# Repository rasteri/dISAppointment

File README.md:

# dISAppointment
Adding ISA slots to modern motherboards

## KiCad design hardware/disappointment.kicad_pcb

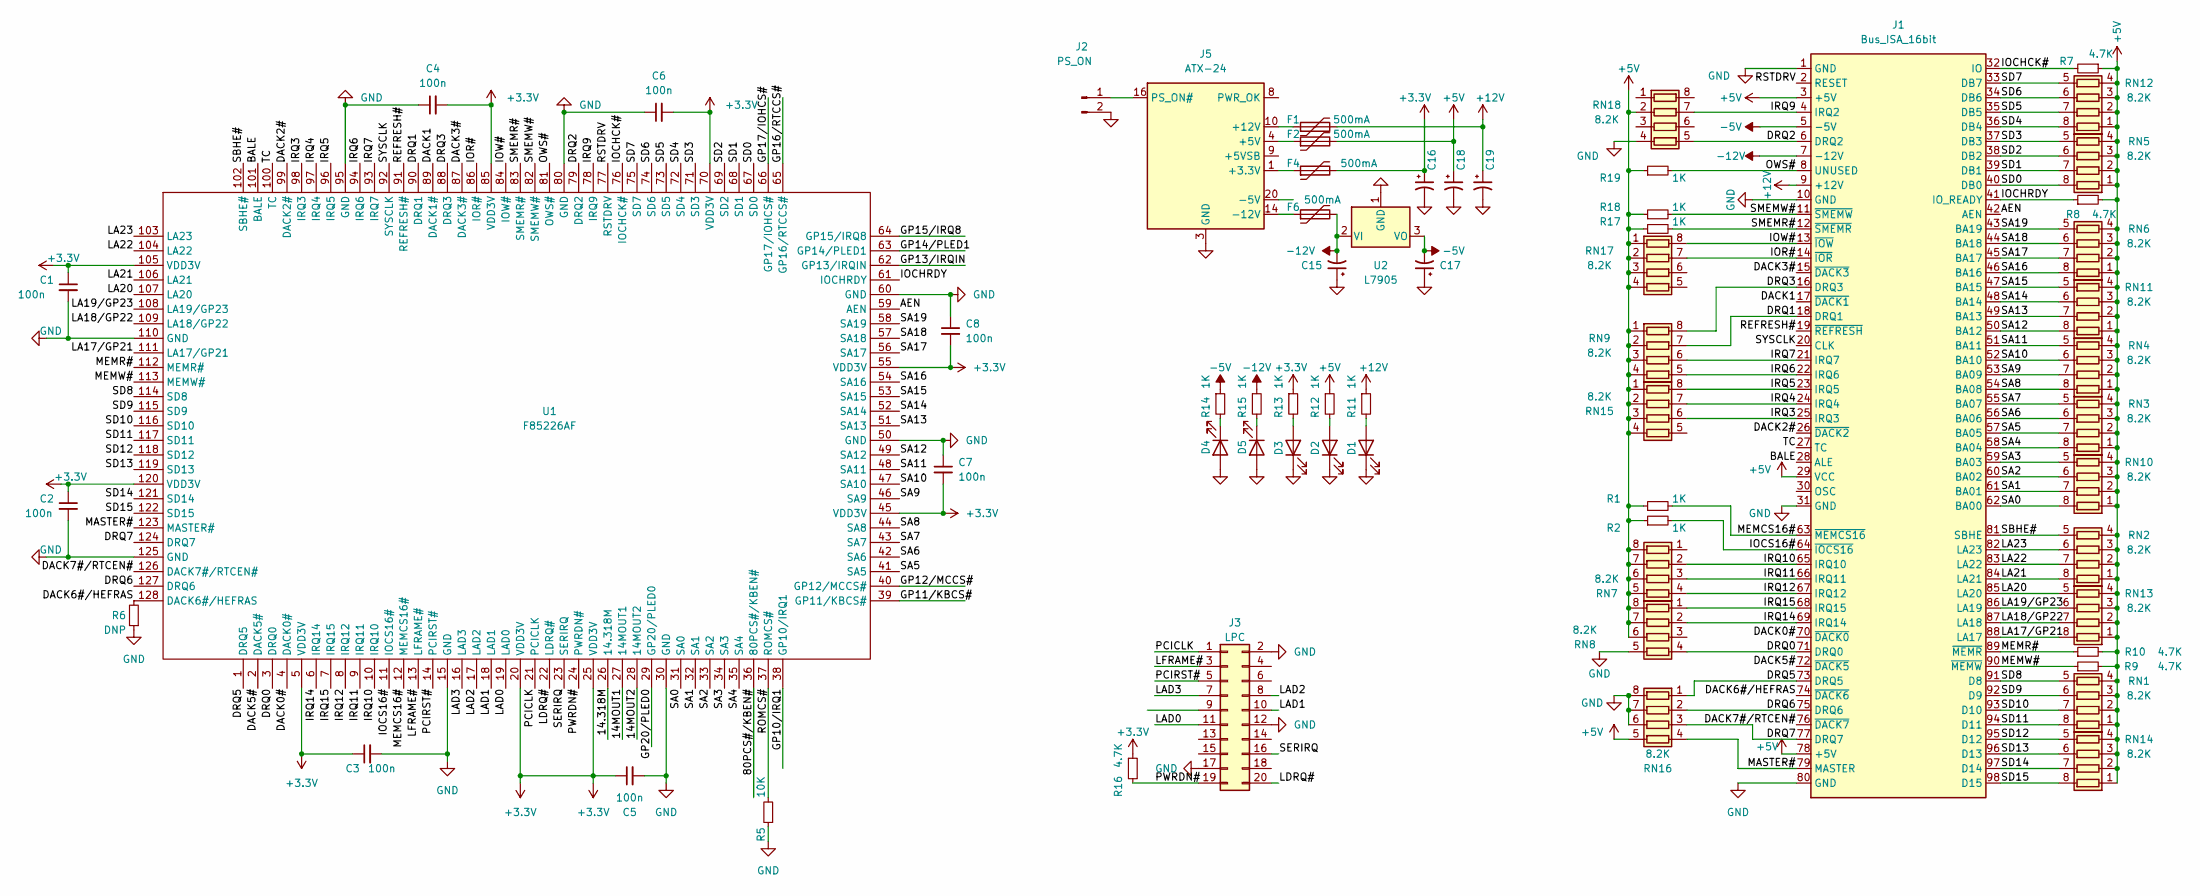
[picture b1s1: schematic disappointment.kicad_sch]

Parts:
C1, C2, C3, C4, C5, C6, C7, C8: 100n; C_1206_3216Metric
C15, C16, C17, C18, C19: 10uF; CP_Radial_D5.0mm_P2.50mm
D1, D2, D3, D4, D5: LED; LED_1206_3216Metric
F1, F2, F4, F6: 500mA; Fuse_1206_3216Metric
J1: Bus_ISA_16bit; ISA
J2: PS_ON; PinHeader_1x02_P2.54mm_Vertical
J3: LPC; PinHeader_2x10_P2.54mm_Vertical
J5: ATX-24; Molex_Mini-Fit_Jr_5566-24A_2x12_P4.20mm_Vertical
R1, R2, R11, R12, R13, R14, R15, R17, R18, R19: 1K; R_1206_3216Metric_Pad1.30x1.75mm_HandSolder
R5: 10K; R_1206_3216Metric_Pad1.30x1.75mm_HandSolder
R6: DNP; R_1206_3216Metric_Pad1.30x1.75mm_HandSolder
R7, R8, R9, R10, R16: 4.7K; R_1206_3216Metric_Pad1.30x1.75mm_HandSolder
RN1, RN2, RN3, RN4, RN5, RN6, RN7, RN8, RN9, RN10, RN11, RN12, RN13, RN14, RN15, RN16, RN17, RN18: 8.2K; R_Array_Concave_4x0603
U1: F85226AF; QFP-26x38_14x20_Pitch0.5mm
U2: L7905; TO-220-3_Vertical

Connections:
+3.3V: C1.1, C2.1, C3.1, C4.2, C5.1, C6.2, C7.2, C8.2, C16.1, F4.2, R13.1, R16.1, U1.5 (VDD3V), U1.20 (VDD3V), U1.25 (VDD3V), U1.45 (VDD3V), U1.55 (VDD3V), U1.70 (VDD3V), U1.85 (VDD3V), U1.105 (VDD3V), U1.120 (VDD3V)
+5V: C18.1, F2.2, J1.3 (+5V), J1.29 (VCC), J1.78 (+5V), R1.1, R2.1, R7.1, R8.2, R9.2, R10.2, R12.1, R17.1, R18.1, R19.1, RN1.1 (R1.1), RN1.2 (R2.1), RN1.3 (R3.1), RN1.4 (R4.1), RN2.1 (R1.1), RN2.2 (R2.1), RN2.3 (R3.1), RN2.4 (R4.1), RN3.1 (R1.1), RN3.2 (R2.1), RN3.3 (R3.1), RN3.4 (R4.1), RN4.1 (R1.1), RN4.2 (R2.1), RN4.3 (R3.1), RN4.4 (R4.1), RN5.1 (R1.1), RN5.2 (R2.1), RN5.3 (R3.1), RN5.4 (R4.1), RN6.1 (R1.1), RN6.2 (R2.1), RN6.3 (R3.1), RN6.4 (R4.1), RN7.5 (R4.2), RN7.6 (R3.2), RN7.7 (R2.2), RN7.8 (R1.2), RN8.6 (R3.2), RN8.7 (R2.2), RN8.8 (R1.2), RN9.1 (R1.1), RN9.2 (R2.1), RN9.3 (R3.1), RN9.4 (R4.1), RN10.1 (R1.1), RN10.2 (R2.1), RN10.3 (R3.1), RN10.4 (R4.1), RN11.1 (R1.1), RN11.2 (R2.1), RN11.3 (R3.1), RN11.4 (R4.1), RN12.1 (R1.1), RN12.2 (R2.1), RN12.3 (R3.1), RN12.4 (R4.1), RN13.1 (R1.1), RN13.2 (R2.1), RN13.3 (R3.1), RN13.4 (R4.1), RN14.1 (R1.1), RN14.2 (R2.1), RN14.3 (R3.1), RN14.4 (R4.1), RN15.1 (R1.1), RN15.2 (R2.1), RN15.3 (R3.1), RN15.4 (R4.1), RN16.5 (R4.2), RN17.1 (R1.1), RN17.2 (R2.1), RN17.3 (R3.1), RN17.4 (R4.1), RN18.2 (R2.1)
+12V: C19.1, F1.2, J1.9 (+12V), R11.1
-5V: C17.2, J1.5 (-5V), R14.1, U2.3 (VO)
-12V: C15.2, F6.2, J1.7 (-12V), R15.1, U2.2 (VI)
/14.318M: U1.26 (14.318M)
/14MOUT1: U1.27 (14MOUT1)
/14MOUT2: U1.28 (14MOUT2)
/80PCS#/KBEN#: U1.36 (80PCS#/KBEN#)
/AEN: J1.42 (AEN), U1.59 (AEN)
/BALE: J1.28 (ALE), U1.101 (BALE)
/DACK0#: J1.70 (~DACK0), U1.4 (DACK0#)
/DACK1: J1.17 (~DACK1), U1.89 (DACK1#)
/DACK2#: J1.26 (~DACK2), U1.99 (DACK2#)
/DACK3#: J1.15 (~DACK3), U1.87 (DACK3#)
/DACK5#: J1.72 (~DACK5), U1.2 (DACK5#)
/DACK6#/HEFRAS: J1.74 (~DACK6), R6.2, U1.128 (DACK6#/HEFRAS)
/DACK7#/RTCEN#: J1.76 (~DACK7), U1.126 (DACK7#/RTCEN#)
/DRQ0: J1.71 (DRQ0), RN8.4 (R4.1), U1.3 (DRQ0)
/DRQ1: J1.18 (DRQ1), RN9.7 (R2.2), U1.90 (DRQ1)
/DRQ2: J1.6 (DRQ2), RN18.5 (R4.2), U1.79 (DRQ2)
/DRQ3: J1.16 (DRQ3), RN9.8 (R1.2), U1.88 (DRQ3)
/DRQ5: J1.73 (DRQ5), RN16.1 (R1.1), U1.1 (DRQ5)
/DRQ6: J1.75 (DRQ6), RN16.2 (R2.1), U1.127 (DRQ6)
/DRQ7: J1.77 (DRQ7), RN16.3 (R3.1), U1.124 (DRQ7)
/GP10/IRQ1: U1.38 (GP10/IRQ1)
/GP11/KBCS#: U1.39 (GP11/KBCS#)
/GP12/MCCS#: U1.40 (GP12/MCCS#)
/GP13/IRQIN: U1.62 (GP13/IRQIN)
/GP14/PLED1: U1.63 (GP14/PLED1)
/GP15/IRQ8: U1.64 (GP15/IRQ8)
/GP16/RTCCS#: U1.65 (GP16/RTCCS#)
/GP17/IOHCS#: U1.66 (GP17/IOHCS#)
/GP20/PLED0: U1.29 (GP20/PLED0)
/IOCHCK#: J1.32 (IO), R7.2, U1.76 (IOCHCK#)
/IOCHRDY: J1.41 (IO_READY), R8.1, U1.61 (IOCHRDY)
/IOCS16#: J1.64 (~IOCS16), R2.2, U1.11 (IOCS16#)
/IOR#: J1.14 (~IOR), RN17.7 (R2.2), U1.86 (IOR#)
/IOW#: J1.13 (~IOW), RN17.8 (R1.2), U1.84 (IOW#)
/IRQ3: J1.25 (IRQ3), RN15.6 (R3.2), U1.98 (IRQ3)
/IRQ4: J1.24 (IRQ4), RN15.7 (R2.2), U1.97 (IRQ4)
/IRQ5: J1.23 (IRQ5), RN15.8 (R1.2), U1.96 (IRQ5)
/IRQ6: J1.22 (IRQ6), RN9.5 (R4.2), U1.94 (IRQ6)
/IRQ7: J1.21 (IRQ7), RN9.6 (R3.2), U1.93 (IRQ7)
/IRQ9: J1.4 (IRQ2), RN18.7 (R2.2), U1.78 (IRQ9)
/IRQ10: J1.65 (IRQ10), RN7.2 (R2.1), U1.10 (IRQ10)
/IRQ11: J1.66 (IRQ11), RN7.3 (R3.1), U1.9 (IRQ11)
/IRQ12: J1.67 (IRQ12), RN7.4 (R4.1), U1.8 (IRQ12)
/IRQ14: J1.69 (IRQ14), RN8.2 (R2.1), U1.6 (IRQ14)
/IRQ15: J1.68 (IRQ15), RN8.1 (R1.1), U1.7 (IRQ15)
/LA17/GP21: J1.88 (LA17), RN13.8 (R1.2), U1.111 (LA17/GP21)
/LA18/GP22: J1.87 (LA18), RN13.7 (R2.2), U1.109 (LA18/GP22)
/LA19/GP23: J1.86 (LA19), RN13.6 (R3.2), U1.108 (LA19/GP23)
/LA20: J1.85 (LA20), RN13.5 (R4.2), U1.107 (LA20)
/LA21: J1.84 (LA21), RN2.8 (R1.2), U1.106 (LA21)
/LA22: J1.83 (LA22), RN2.7 (R2.2), U1.104 (LA22)
/LA23: J1.82 (LA23), RN2.6 (R3.2), U1.103 (LA23)
/LAD0: J3.11, U1.19 (LAD0)
/LAD1: J3.10, U1.18 (LAD1)
/LAD2: J3.8, U1.17 (LAD2)
/LAD3: J3.7, U1.16 (LAD3)
/LDRQ#: J3.20, U1.22 (LDRQ#)
/LFRAME#: J3.3, U1.13 (LFRAME#)
/MASTER#: J1.79 (MASTER), RN16.4 (R4.1), U1.123 (MASTER#)
/MEMCS16#: J1.63 (~MEMCS16), R1.2, U1.12 (MEMCS16#)
/MEMR#: J1.89 (~MEMR), R10.1, U1.112 (MEMR#)
/MEMW#: J1.90 (~MEMW), R9.1, U1.113 (MEMW#)
/OWS#: J1.8 (UNUSED), R19.2, U1.81 (OWS#)
/PCICLK: J3.1, U1.21 (PCICLK)
/PCIRST#: J3.5, U1.14 (PCIRST#)
/PWRDN#: J3.19, R16.2, U1.24 (PWRDN#)
/REFRESH#: J1.19 (~REFRESH), U1.91 (REFRESH#)
/ROMCS#: R5.2, U1.37 (ROMCS#)
/RSTDRV: J1.2 (RESET), U1.77 (RSTDRV)
/SA0: J1.62 (BA00), RN10.8 (R1.2), U1.31 (SA0)
/SA1: J1.61 (BA01), RN10.7 (R2.2), U1.32 (SA1)
/SA2: J1.60 (BA02), RN10.6 (R3.2), U1.33 (SA2)
/SA3: J1.59 (BA03), RN10.5 (R4.2), U1.34 (SA3)
/SA4: J1.58 (BA04), RN3.8 (R1.2), U1.35 (SA4)
/SA5: J1.57 (BA05), RN3.7 (R2.2), U1.41 (SA5)
/SA6: J1.56 (BA06), RN3.6 (R3.2), U1.42 (SA6)
/SA7: J1.55 (BA07), RN3.5 (R4.2), U1.43 (SA7)
/SA8: J1.54 (BA08), RN4.8 (R1.2), U1.44 (SA8)
/SA9: J1.53 (BA09), RN4.7 (R2.2), U1.46 (SA9)
/SA10: J1.52 (BA10), RN4.6 (R3.2), U1.47 (SA10)
/SA11: J1.51 (BA11), RN4.5 (R4.2), U1.48 (SA11)
/SA12: J1.50 (BA12), RN11.8 (R1.2), U1.49 (SA12)
/SA13: J1.49 (BA13), RN11.7 (R2.2), U1.51 (SA13)
/SA14: J1.48 (BA14), RN11.6 (R3.2), U1.52 (SA14)
/SA15: J1.47 (BA15), RN11.5 (R4.2), U1.53 (SA15)
/SA16: J1.46 (BA16), RN6.8 (R1.2), U1.54 (SA16)
/SA17: J1.45 (BA17), RN6.7 (R2.2), U1.56 (SA17)
/SA18: J1.44 (BA18), RN6.6 (R3.2), U1.57 (SA18)
/SA19: J1.43 (BA19), RN6.5 (R4.2), U1.58 (SA19)
/SBHE#: J1.81 (SBHE), RN2.5 (R4.2), U1.102 (SBHE#)
/SD0: J1.40 (DB0), RN5.8 (R1.2), U1.67 (SD0)
/SD1: J1.39 (DB1), RN5.7 (R2.2), U1.68 (SD1)
/SD2: J1.38 (DB2), RN5.6 (R3.2), U1.69 (SD2)
/SD3: J1.37 (DB3), RN5.5 (R4.2), U1.71 (SD3)
/SD4: J1.36 (DB4), RN12.8 (R1.2), U1.72 (SD4)
/SD5: J1.35 (DB5), RN12.7 (R2.2), U1.73 (SD5)
/SD6: J1.34 (DB6), RN12.6 (R3.2), U1.74 (SD6)
/SD7: J1.33 (DB7), RN12.5 (R4.2), U1.75 (SD7)
/SD8: J1.91 (D8), RN1.5 (R4.2), U1.114 (SD8)
/SD9: J1.92 (D9), RN1.6 (R3.2), U1.115 (SD9)
/SD10: J1.93 (D10), RN1.7 (R2.2), U1.116 (SD10)
/SD11: J1.94 (D11), RN1.8 (R1.2), U1.117 (SD11)
/SD12: J1.95 (D12), RN14.5 (R4.2), U1.118 (SD12)
/SD13: J1.96 (D13), RN14.6 (R3.2), U1.119 (SD13)
/SD14: J1.97 (D14), RN14.7 (R2.2), U1.121 (SD14)
/SD15: J1.98 (D15), RN14.8 (R1.2), U1.122 (SD15)
/SERIRQ: J3.16, U1.23 (SERIRQ)
/SMEMR#: J1.12 (~SMEMR), R17.2, U1.83 (SMEMR#)
/SMEMW#: J1.11 (~SMEMW), R18.2, U1.82 (SMEMW#)
/SYSCLK: J1.20 (CLK), U1.92 (SYSCLK)
/TC: J1.27 (TC), U1.100 (TC)
GND: C1.2, C2.2, C3.2, C4.1, C5.2, C6.1, C7.1, C8.1, C15.1, C16.2, C17.1, C18.2, C19.2, D1.1 (K), D2.1 (K), D3.1 (K), D4.2 (A), D5.2 (A), J1.1 (GND), J1.10 (GND), J1.31 (GND), J1.80 (GND), J2.2, J3.2, J3.12, J3.17, J5.3 (GND), J5.5 (GND), J5.7 (GND), J5.15 (GND), J5.17 (GND), J5.18 (GND), J5.19 (GND), J5.24 (GND), R5.1, R6.1, RN8.5 (R4.2), RN16.6 (R3.2), RN16.7 (R2.2), RN16.8 (R1.2), RN18.4 (R4.1), U1.15 (GND), U1.30 (GND), U1.50 (GND), U1.60 (GND), U1.80 (GND), U1.95 (GND), U1.110 (GND), U1.125 (GND), U2.1 (GND)
unnamed: D1.2 (A), R11.2
unnamed: D2.2 (A), R12.2
unnamed: D3.2 (A), R13.2
unnamed: D4.1 (K), R14.2
unnamed: D5.1 (K), R15.2
unnamed: F1.1, J5.10 (+12V), J5.11 (+12V)
unnamed: F2.1, J5.4 (+5V), J5.6 (+5V), J5.21 (+5V), J5.22 (+5V), J5.23 (+5V)
unnamed: F4.1, J5.1 (+3.3V), J5.2 (+3.3V), J5.12 (+3.3V), J5.13 (+3.3V)
unnamed: J2.1, J5.16 (PS_ON#)
unnamed: F6.1, J5.14 (-12V)

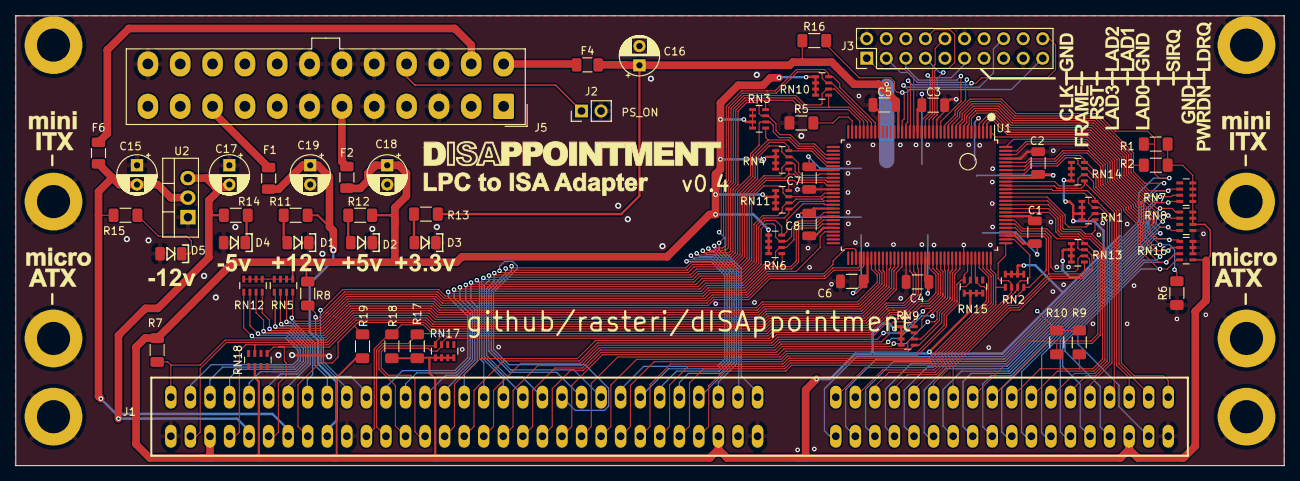
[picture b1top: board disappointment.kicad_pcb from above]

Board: 2 copper layers, 164.7 x 58.4 mm, 63 parts (0 on the bottom side), 114 nets.

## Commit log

2023-03-21 Hardware
2023-03-21 Software
2023-03-21 Create LICENSE
2023-05-14 started rerouting PCB
2023-05-20 getting there
2023-05-24 getting there more
2023-06-15 about done
2023-06-15 cleanup
2023-06-17 LEDs, -5v regulator
2023-06-18 pson
2023-06-29 cleanups
2023-06-29 gitignore
2023-08-16 what a... letdown?
2023-11-12 added the correct resistors
2025-01-30 silkscreen cleanup
